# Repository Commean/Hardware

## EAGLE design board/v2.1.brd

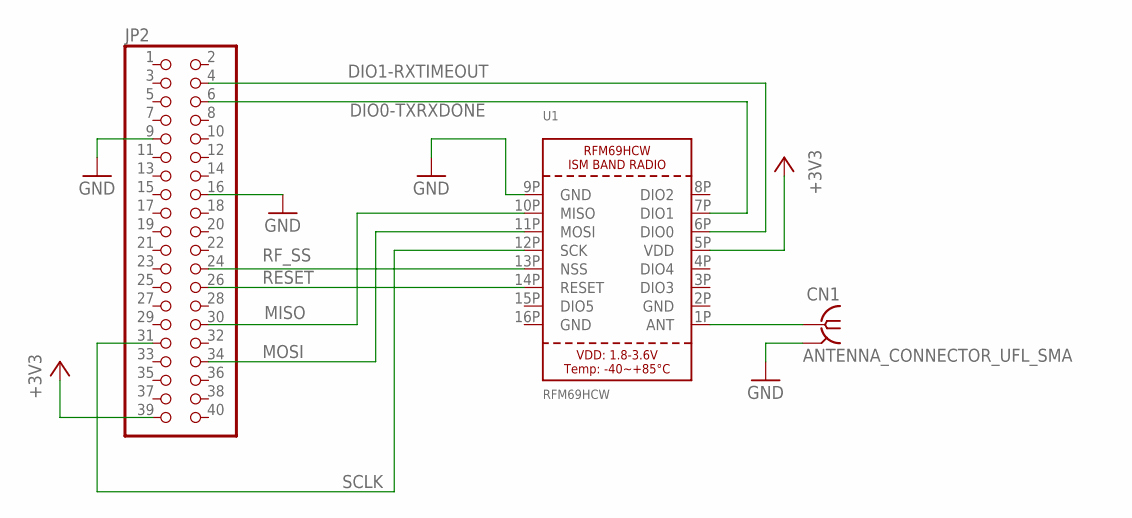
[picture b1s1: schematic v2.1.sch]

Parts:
CN1: ANTENNA_CONNECTOR_UFL_SMA
JP2: PINHD-2X20; 2X20
U1: RFM69HCW; RFMHCW_SMT

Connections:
+3V3: JP2.39, U1.5P (VDD)
DIO0-TXRXDONE: JP2.6, U1.7P (DIO1)
DIO1-RXTIMEOUT: JP2.4, U1.6P (DIO0)
GND: CN1.GND, CN1.GND@1 (GND), CN1.GND@2 (GND), CN1.GND@3 (GND), JP2.9, JP2.16, U1.2P (GND), U1.9P (GND), U1.16P (GND)
MISO: JP2.30, U1.10P (MISO)
MOSI: JP2.34, U1.11P (MOSI)
unnamed: CN1.SIGNAL (1), U1.1P (ANT)
RESET: JP2.26, U1.14P (RESET)
RF_SS: JP2.24, U1.13P (NSS)
SCLK: JP2.31, U1.12P (SCK)

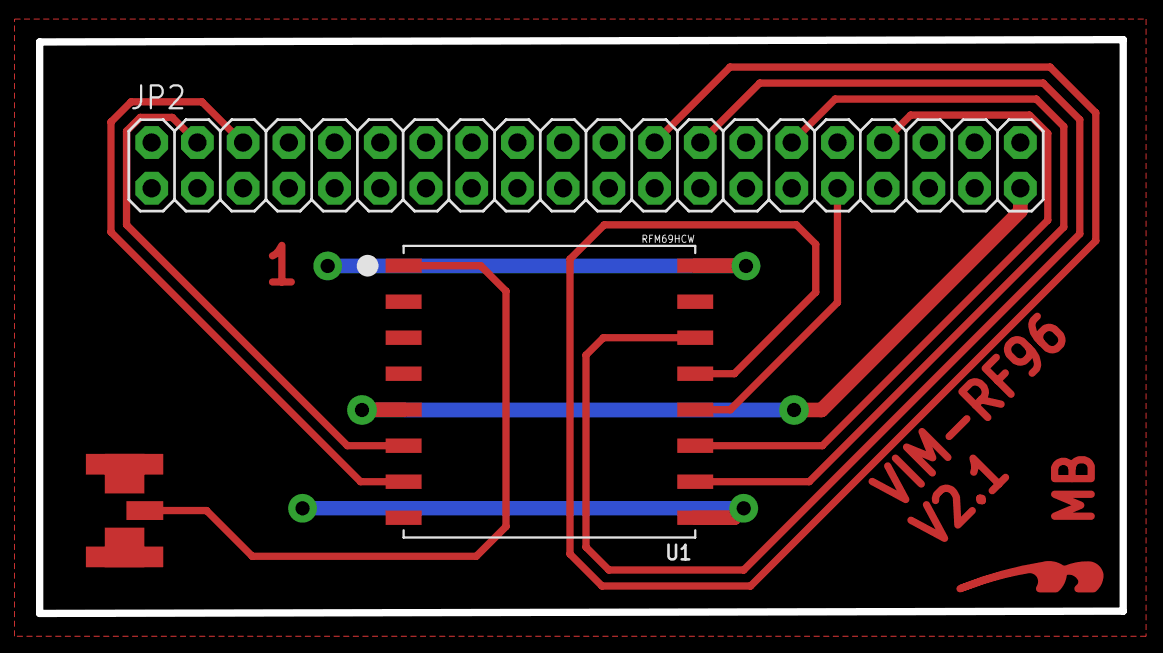
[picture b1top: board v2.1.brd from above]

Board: 2 copper layers, 60.2 x 31.9 mm, 4 parts (0 on the bottom side), 10 nets.

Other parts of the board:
U$1: LOGOTOP_8

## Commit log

2021-12-07 The raw program for sending and receiving data.
2021-12-07 Upload New File
2021-12-07 This program receives the traffic data as a String and sends it on a website in JSON-Format
2021-12-15 Add project
2021-12-15 Add gitignore
2021-12-15 Extend gitignore
2021-12-15 Mächtig
2022-02-04 Init
2022-02-05 Add lmic_project_config.h
2022-02-05 Use build_flags
2022-02-05 Add DIOs again
2022-02-05 Specifiy DIO1
2022-02-05 Update band
2022-02-05 Add Template
2022-02-08 Update message
2022-02-08 Add scripts for API
    (Insomnia)
2022-03-13 Add support for heltec_wifi_lora_32
2022-03-13 Generate random data
2022-03-15 Replace char[] with string
2022-03-21 Add board

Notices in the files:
parts and their libraries:
microbuilder: This work is placed in the public domain, and may be freely used for commercial and non-commercial work with the following conditions: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
